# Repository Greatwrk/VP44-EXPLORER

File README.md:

# VP44 EXPLORER

My project replaces the control board that sits on top of the pump with a remote board.
The project uses an STM32f303 Nucleo dev. Board and I used Arduino IDE.
A custom PCB was made in two parts. One is the main logic and sensor interface. The second part is the 
solenoid drivers and power supply. The current driver board uses a high-speed switching buck converter
to operate the fuel solenoid. A linear drive board is under development.
The linear method is the OEM style. It generates a lot of heat and is cooled by the fuel flowing
under it in the pump housing. The switching method results in significantly less heat. The downside is the switching signal can
mask the current monitoring of the solenoid. As the armature plunger moves it causes a change in inductance which causes a small current blip.
The blip is useful to determine the solenoid dead time.

The VP44 shaft has a toothed wheel, the tooth spacing is 3 degrees of crankshaft rotation.
Every 60 degrees (120 at crankshaft) is a pair of staggered teeth.
These I refer to as the index tooth.
A dual magneto-resistive sensor with a back bias magnet senses the teeth as they pass by and creates two sinewaves.
The one that leads I refer to as phase A. The second follows by approximately 90 degrees, I refer to it as phase B.
Both signals are adaptive zero crossing detected by internal opAmps and the DACs in the STM32 and then fed to timer captures.
The software detects the index tooth region and resets a tooth edge counter to zero.
On the tooth edge 19 of the B phase the radial injection plungers are at their maximum extension.
As they follow the cam ring into compression it's at this position the injection solenoid valve must be fully transitioned to the closed position.
This is the start of injection SOI. After a variable amount of degrees, the valve de-energizes this is the end of injection EOI.

Since the solenoid has deadtime on both turn on and turn off the switching must occur before edge 19 or EOI actually happens.
This is done by computing shaft position, velocity, and acceleration to predict the relative time from a current tooth edge to edge 19.
Obviously, the closer we are to the edge 19 event the better the prediction will be, but at higher RPMs the deadtime of the solenoid results in the required prediction to
occur many degrees in advance else the valve will be closed too late or early.
That results in late injection, reduced fuel delivery and hazy smoke.
The valve must be de-energized before the moment of desired EOI because of mechanical delay I call this release time, which is about 850 microseconds.
The dead time is mostly dependent on the battery voltage and must be calculated often. 
A full current is applied to get the valve moving then the current is reduced to prevent the valve from slamming on its seat and bouncing.
Finally, the current is reduced to a safe level for the majority of the injection event.
The switch-off induction spike at EOI must be clamped at a higher voltage and low current for a fast release.
The magnetic field is determined largely by A x N turns, so keeping current low speeds the armature release.
Simple clamping / recirculating methods are too slow. A zener diode RC circuit is used. 
Some manual adjustments to times and current values must be determined with an oscilloscope and are stored.

Anyone who has kick-started or rope-started a small engine has experienced the rapid fluctuations that occur in 
crankshaft velocity. These also occur in a running engine but are greatly reduced by the flywheel mass
and inertia. These variations have to be accounted for in both the SOI time and EOI time if not the
engine will start to run rough which makes the variations worse and results in timing and delivery
errors and possible stalling or running away.

The timing advance is determined by the phase relationship of the cam ring to the crankshaft position.
The ECU decodes the crankshaft position sensor and cam sensor to create a reference signal that
occurs at 20 degrees after top dead center for each cylinder. Later engines removed the CKP and changed the camshaft gear. 
With my project, the decoding is done internally and the ECU is not required. 
The cam ring moves by a hydraulic piston which is controlled by another solenoid valve. It is PWM controlled by the MCU. 
The actual timing is calculated by the VP tooth signal phase relationship to the CKP-derived signal. 
A software servo control loop adjusts the PWM to match the computed timing with the desired timing contained in the usual look-up tables.

For now, the TPS, MAP and CKP are all that's required. The CMP is optional. A CAN interface is on the board and a CAN interface is being developed.
The Schematic and PCB were made with KiCad. The code has some low-level stuff for some of the peripherals that at the time were not supported by STM32duino.

If you build this I suggest using a 2 ohm 50 W resistor in place of the fuel solenoid for testing with a scope. The resistor can later be placed
in series with the solenoid to protect it on the bench while sweep testing at RPMs and Fuel levels. Listen for any malfunctions.
The power transistors must be isolated from the heatsink with silicon insulators. Always test isolation with an DVM.

# See it run [HERE](https://www.youtube.com/watch?v=DHwnkv7ZLJk)

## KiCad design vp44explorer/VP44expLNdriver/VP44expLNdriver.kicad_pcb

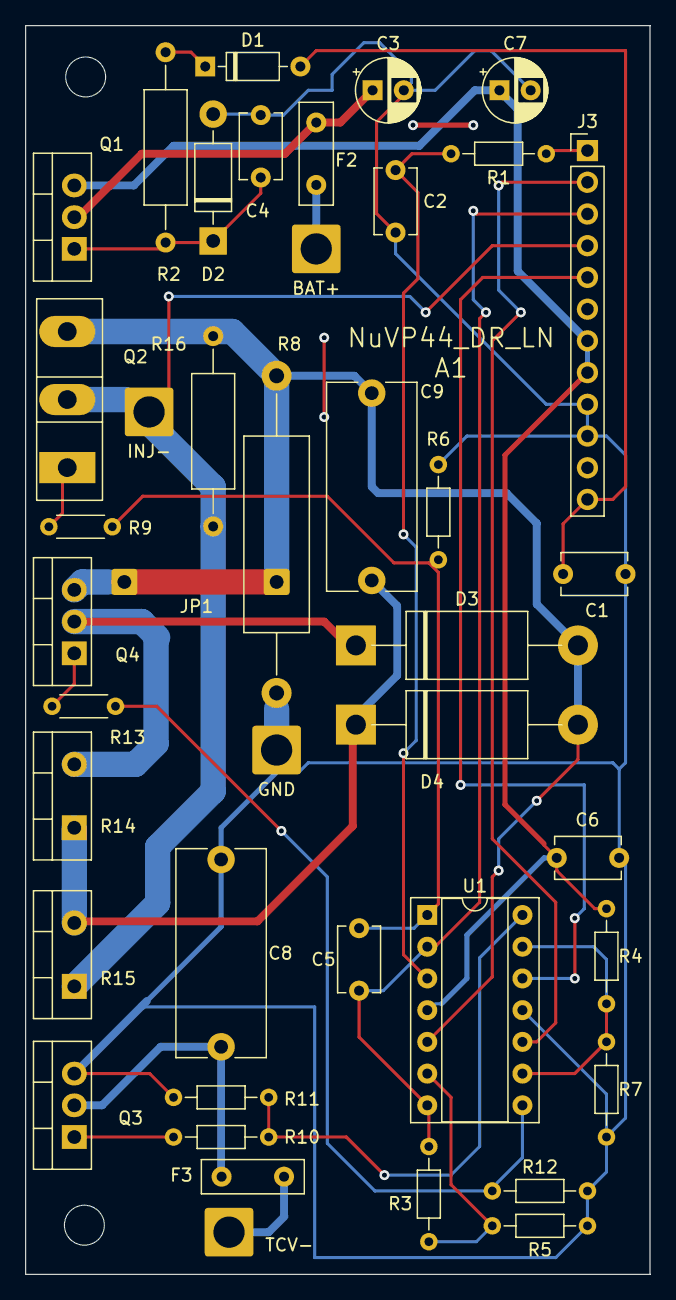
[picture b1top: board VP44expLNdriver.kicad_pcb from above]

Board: 2 copper layers, 50.0 x 100.0 mm, 45 parts (0 on the bottom side), 26 nets.

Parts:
C1, C4: 1uF; C_Disc_D5.1mm_W3.2mm_P5.00mm
C2, C6: 0.1uF; C_Disc_D5.1mm_W3.2mm_P5.00mm
C3, C7: 100uF; CP_Radial_D5.0mm_P2.50mm
C5: 100pF; C_Disc_D5.1mm_W3.2mm_P5.00mm
C8: 1uF; C_Rect_L16.5mm_W7.0mm_P15.00mm_MKT
C9: 0.1uF; C_Rect_L16.5mm_W7.0mm_P15.00mm_MKT
D1: 1N914B; D_DO-35_SOD27_P7.62mm_Horizontal
D2: 5.6V; D_DO-41_SOD81_P10.16mm_Horizontal
D3, D4: 31V; D_DO-201AD_P17.78mm_Horizontal
F2, F3: Polyfuse; C_Disc_D8.0mm_W2.5mm_P5.00mm
J1: GND; SolderWire-2sqmm_1x01_D2mm_OD3.9mm
J2: BAT+; SolderWire-2sqmm_1x01_D2mm_OD3.9mm
J3: Conn_01x12; PinHeader_1x12_P2.54mm_Vertical
J4: INJ-; SolderWire-2sqmm_1x01_D2mm_OD3.9mm
J5: TCV-; SolderWire-2sqmm_1x01_D2mm_OD3.9mm
J6, J7: TCV; SolderWire-0.5sqmm_1x01_D0.9mm_OD2.1mm
MH1, MH2: MountingHole_3.2mm_M3
Q1: MJF44H11G; TO-220-3_Vertical
Q2: IRF250P225; TO-247-3_Vertical
Q3: IRL2910; TO-220-3_Vertical
Q4: 75NF20; TO-220-3_Vertical
R1, R3, R4, R5, R6, R7, R11, R12: 10K; R_Axial_DIN0204_L3.6mm_D1.6mm_P7.62mm_Horizontal
R2, R16: 220R; R_Axial_DIN0309_L9.0mm_D3.2mm_P15.24mm_Horizontal
R8: .05R; R_Axial_DIN0516_L15.5mm_D5.0mm_P25.40mm_Horizontal
R9, R13: 100R; R_Axial_DIN0204_L3.6mm_D1.6mm_P5.08mm_Horizontal
R10: 100R; R_Axial_DIN0204_L3.6mm_D1.6mm_P7.62mm_Horizontal
R14, R15: 1R; TO-220-2_Vertical
U1: Opamp_Quad; DIP-14_W7.62mm_Socket

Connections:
+5V: C6.2, C7.1, J3.7, J3.8, Q1.3 (E), R4.1, U1.4 (V+)
+12V: C1.2, D1.2 (A), J3.12
GND: C1.1, C2.1, C3.2, C4.1, C6.1, C7.2, C8.1, D2.2 (A), J1.1, J3.9, J3.10, Q3.3 (S), R5.1, R6.2, R7.2, R8.2, R11.2, R12.2, U1.11 (V-)
unnamed: C5.2, R6.1, R9.1, U1.1
unnamed: D1.1 (K), R2.1
unnamed: C4.2, D2.1 (K), Q1.1 (B), R2.2
unnamed: C9.1, D3.2 (A), D4.2 (A), J6.1, J7.1, Q2.3 (S), Q4.3 (S), R8.1, R16.1, U1.5 (+)
unnamed: D3.1 (K), Q4.2 (D), R14.2
unnamed: C9.2, D4.1 (K), R14.1, R15.2
unnamed: F2.1, J2.1
unnamed: J3.1, R1.1
unnamed: J3.2, U1.10 (+)
unnamed: C5.1, J3.3, R3.1, U1.2 (-), U1.7
unnamed: J3.4, J4.1, Q2.2 (D), R15.1, R16.2
unnamed: J3.5, U1.12 (+)
unnamed: F3.2, J5.1
unnamed: C3.1, F2.2, Q1.2 (C)
unnamed: Q2.1 (G), R9.2
unnamed: C8.2, F3.1, Q3.2 (D)
unnamed: Q3.1 (G), R10.2
unnamed: Q4.1 (G), R13.1
unnamed: R10.1, R11.1, U1.14
unnamed: R12.1, R13.2, U1.8
unnamed: C2.2, R1.2, U1.3 (+)
unnamed: R3.2, R5.2, U1.6 (-)
unnamed: R4.2, R7.1, U1.9 (-), U1.13 (-)

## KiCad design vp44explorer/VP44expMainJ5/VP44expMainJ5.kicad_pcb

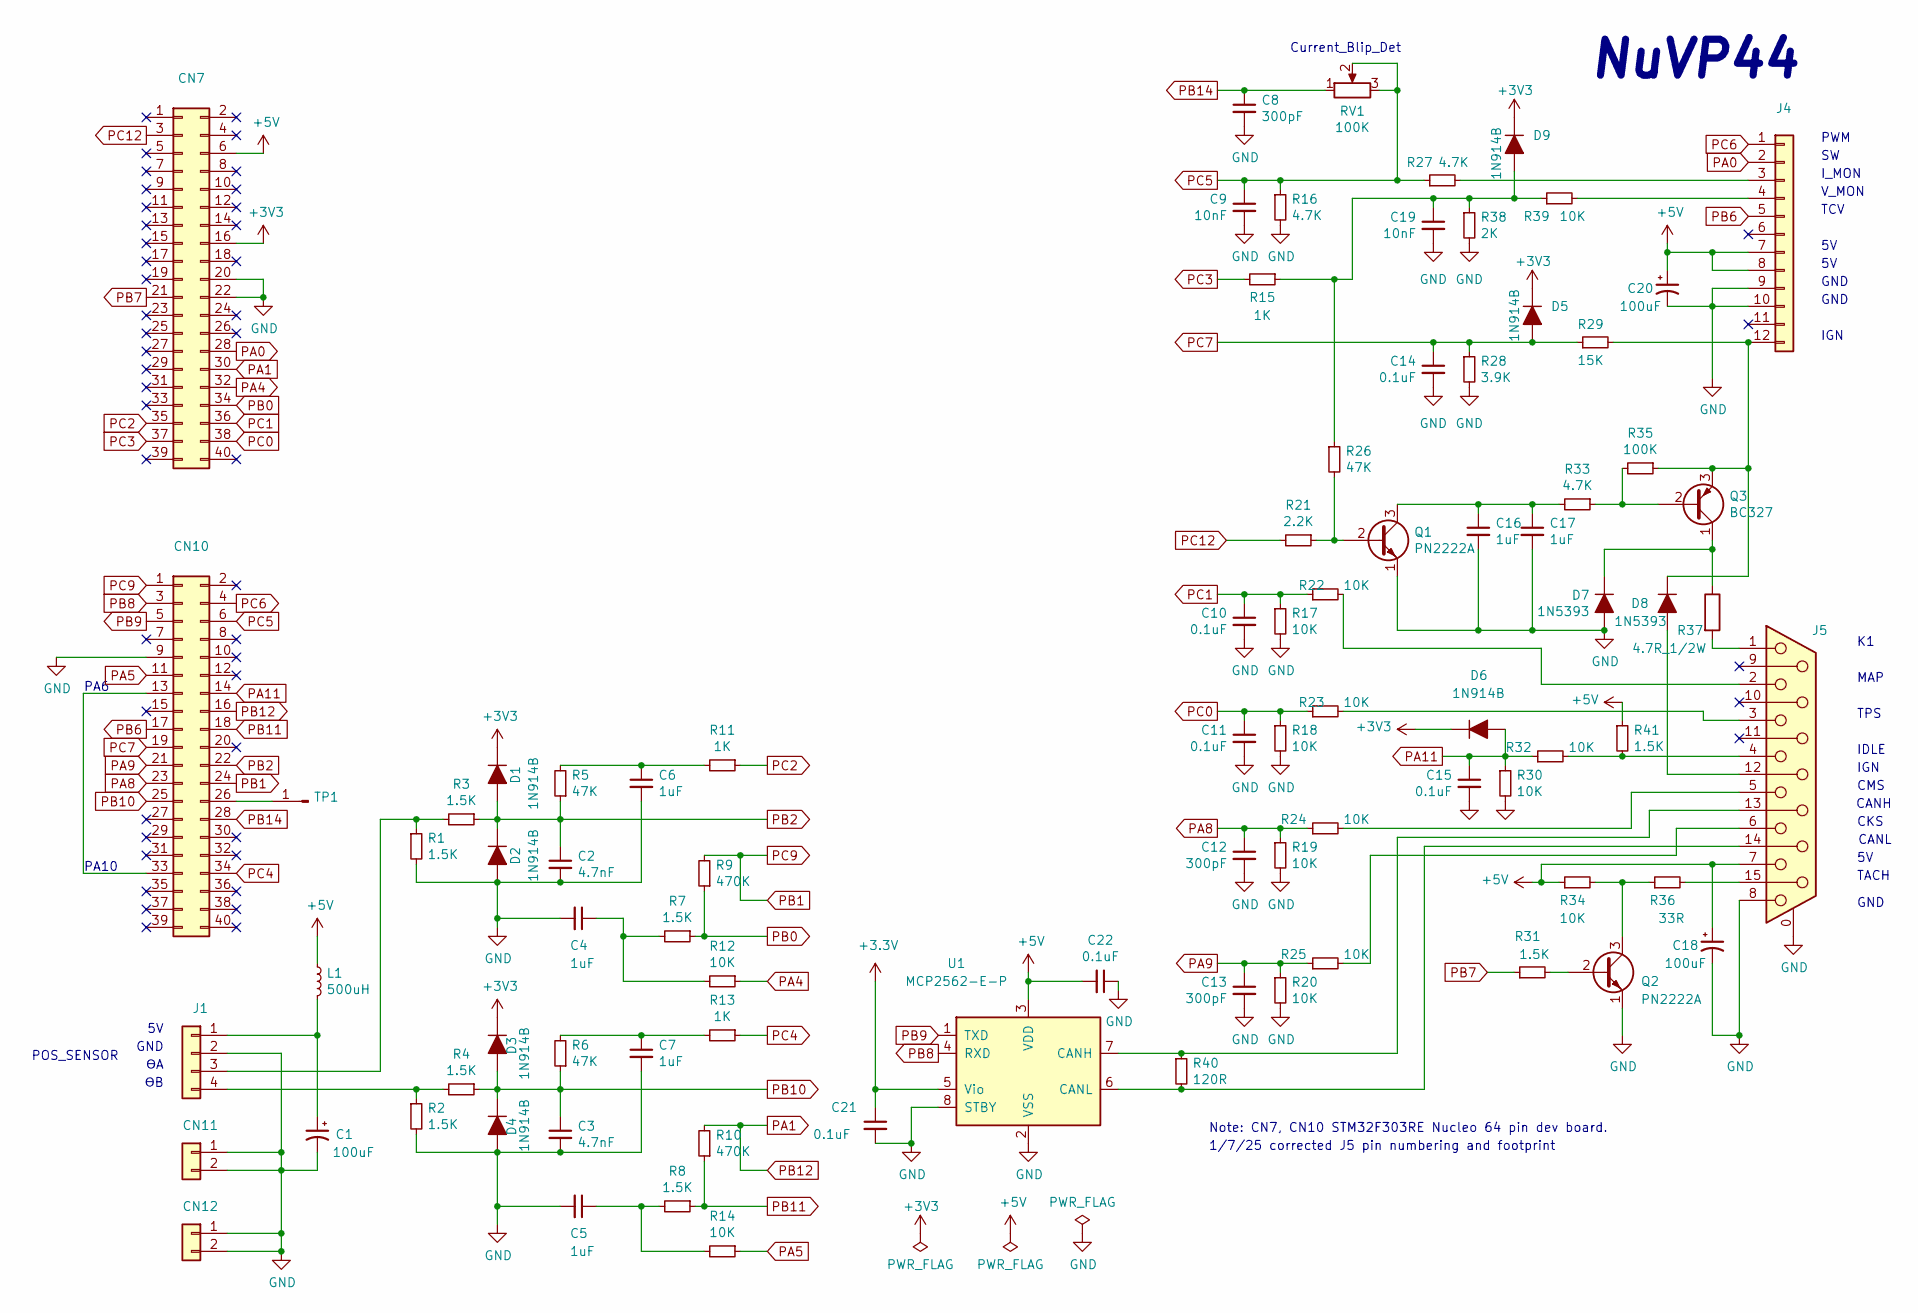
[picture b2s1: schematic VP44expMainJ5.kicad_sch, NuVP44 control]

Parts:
C1, C18, C20: 100uF; CP_Radial_D5.0mm_P2.50mm
C2, C3: 4.7nF; C_Disc_D5.0mm_W2.5mm_P5.00mm
C4, C5, C6, C7, C16, C17: 1uF; C_Disc_D5.1mm_W3.2mm_P5.00mm
C8, C12, C13: 300pF; C_Disc_D5.0mm_W2.5mm_P5.00mm
C9, C19: 10nF; C_Disc_D5.0mm_W2.5mm_P5.00mm
C10, C11, C14, C15, C21, C22: 0.1uF; C_Disc_D5.0mm_W2.5mm_P5.00mm
CN7, CN10: Conn_02x20_Odd_Even; PinHeader_2x20_P2.54mm_Vertical
CN11, CN12: Conn_01x02_Female; PinHeader_1x02_P2.54mm_Vertical
D1, D2, D3, D4, D5, D6, D9: 1N914B; D_DO-35_SOD27_P7.62mm_Horizontal
D7, D8: 1N5393; D_DO-41_SOD81_P12.70mm_Horizontal
J1: Conn_01x04_Shielded; PinHeader_1x04_P2.54mm_Vertical
J4: Conn_01x12; PinHeader_1x12_P2.54mm_Vertical
J5: DSUB-15_Female_Horizontal_P2.77x2.84mm_EdgePinOffset4.94mm_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
L1: 500uH; L_Axial_L11.0mm_D4.5mm_P5.08mm_Vertical_Fastron_MECC
Q1, Q2: PN2222A; TO-92_Inline
Q3: BC327; TO-92_Inline
R1, R2, R3, R4, R7, R8, R31, R41: 1.5K; R_Axial_DIN0204_L3.6mm_D1.6mm_P7.62mm_Horizontal
R5, R6, R26: 47K; R_Axial_DIN0204_L3.6mm_D1.6mm_P7.62mm_Horizontal
R9, R10: 470K; R_Axial_DIN0204_L3.6mm_D1.6mm_P7.62mm_Horizontal
R11, R13, R15: 1K; R_Axial_DIN0204_L3.6mm_D1.6mm_P7.62mm_Horizontal
R12, R14, R17, R18, R19, R20, R22, R23, R24, R25, R30, R32, R34, R39: 10K; R_Axial_DIN0204_L3.6mm_D1.6mm_P7.62mm_Horizontal
R16, R27, R33: 4.7K; R_Axial_DIN0204_L3.6mm_D1.6mm_P7.62mm_Horizontal
R21: 2.2K; R_Axial_DIN0204_L3.6mm_D1.6mm_P7.62mm_Horizontal
R28: 3.9K; R_Axial_DIN0204_L3.6mm_D1.6mm_P7.62mm_Horizontal
R29: 15K; R_Axial_DIN0204_L3.6mm_D1.6mm_P7.62mm_Horizontal
R35: 100K; R_Axial_DIN0204_L3.6mm_D1.6mm_P7.62mm_Horizontal
R36: 33R; R_Axial_DIN0204_L3.6mm_D1.6mm_P7.62mm_Horizontal
R37: 4.7R_1/2W; R_Axial_DIN0309_L9.0mm_D3.2mm_P15.24mm_Horizontal
R38: 2K; R_Axial_DIN0204_L3.6mm_D1.6mm_P7.62mm_Horizontal
R40: 120R; R_Axial_DIN0204_L3.6mm_D1.6mm_P7.62mm_Horizontal
RV1: 100K; Potentiometer_Bourns_3296W_Vertical
TP1: Conn_01x01_Male; PinHeader_1x01_P2.54mm_Vertical
U1: MCP2562-E-P; DIP-8_W7.62mm_Socket

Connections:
+5V: C18.1, C20.1, C22.2, CN7.6, J4.7, J4.8, J5.7, L1.1, R34.1, R41.1, U1.3 (VDD)
GND: C1.2, C2.2, C3.2, C4.2, C5.2, C6.2, C7.2, C8.2, C9.2, C10.2, C11.2, C12.2, C13.2, C14.2, C15.2, C16.2, C17.2, C18.2, C19.2, C20.2, C21.2, C22.1, CN7.20, CN7.22, CN10.9, CN11.1, CN11.2, CN12.1, CN12.2, D2.2 (A), D4.2 (A), D7.2 (A), J1.2, J4.9, J4.10, J5.0 (PAD), J5.8, Q1.1 (E), Q2.1 (E), R1.2, R2.2, R16.2, R17.2, R18.2, R19.2, R20.2, R28.2, R30.2, R38.2, U1.2 (VSS), U1.8 (STBY)
unnamed: C4.1, R7.2, R12.2
unnamed: C5.1, R8.2, R14.2
unnamed: C6.1, R5.2, R11.2
unnamed: C7.1, R6.2, R13.2
unnamed: CN10.13, CN10.33
unnamed: CN10.26, TP1.1
unnamed: D7.1 (K), Q3.1 (C), R37.1
unnamed: D8.2 (A), J5.12
unnamed: D8.1 (K), J4.12, Q3.3 (E), R29.2, R35.1
unnamed: C19.1, D9.2 (A), R15.1, R26.1, R38.1, R39.1
unnamed: C1.1, J1.1, L1.2
unnamed: J1.3, R1.1, R3.2
unnamed: J1.4, R2.1, R4.2
unnamed: J4.3, R27.2
unnamed: J4.4, R39.2
unnamed: J5.13, R40.1, U1.7 (CANH)
unnamed: J5.14, R40.2, U1.6 (CANL)
unnamed: J5.15, R36.2
unnamed: J5.1, R37.2
unnamed: J5.2, R22.2
unnamed: J5.3, R23.2
unnamed: J5.4, R32.2, R41.2
unnamed: J5.5, R24.2
unnamed: J5.6, R25.2
unnamed: Q1.2 (B), R21.1, R26.2
unnamed: C16.1, C17.1, Q1.3 (C), R33.2
unnamed: Q2.2 (B), R31.2
unnamed: Q2.3 (C), R34.2, R36.1
unnamed: Q3.2 (B), R33.1, R35.2
PA0: CN7.28, J4.2
PA1: CN7.30, CN10.16, R10.2
PA4: CN7.32, R12.1
PA5: CN10.11, R14.1
PA8: C12.1, CN10.23, R19.1, R24.1
PA9: C13.1, CN10.21, R20.1, R25.1
PA11: C15.1, CN10.14, D6.2 (A), R30.1, R32.1
PB0: CN7.34, R7.1, R9.1
PB1: CN10.1, CN10.24, R9.2
PB2: C2.1, CN10.22, D1.2 (A), D2.1 (K), R3.1, R5.1
PB6: CN10.17, J4.5
PB7: CN7.21, R31.1
PB8: CN10.3, U1.4 (RXD)
PB9: CN10.5, U1.1 (TXD)
PB10: C3.1, CN10.25, D3.2 (A), D4.1 (K), R4.1, R6.1
PB11: CN10.18, R8.1, R10.1
PB14: C8.1, CN10.28, RV1.1
PC0: C11.1, CN7.38, R18.1, R23.1
PC1: C10.1, CN7.36, R17.1, R22.1
PC2: CN7.35, R11.1
PC3: CN7.37, R15.2
PC4: CN10.34, R13.1
PC5: C9.1, CN10.6, R16.1, R27.1, RV1.2, RV1.3
PC6: CN10.4, J4.1
PC7: C14.1, CN10.19, D5.2 (A), R28.1, R29.1
PC12: CN7.3, R21.2

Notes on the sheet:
Note: CN7, CN10 STM32F303RE Nucleo 64 pin dev board.
IGN
GND
I_MON
CANL
PA10
NuVP44
Current_Blip_Det
PA6
CMS
TCV
TACH
1/7/25 corrected J5 pin numbering and footprint
V_MON
IDLE
PWM
POS_SENSOR
CKS
TPS
MAP
CANH

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
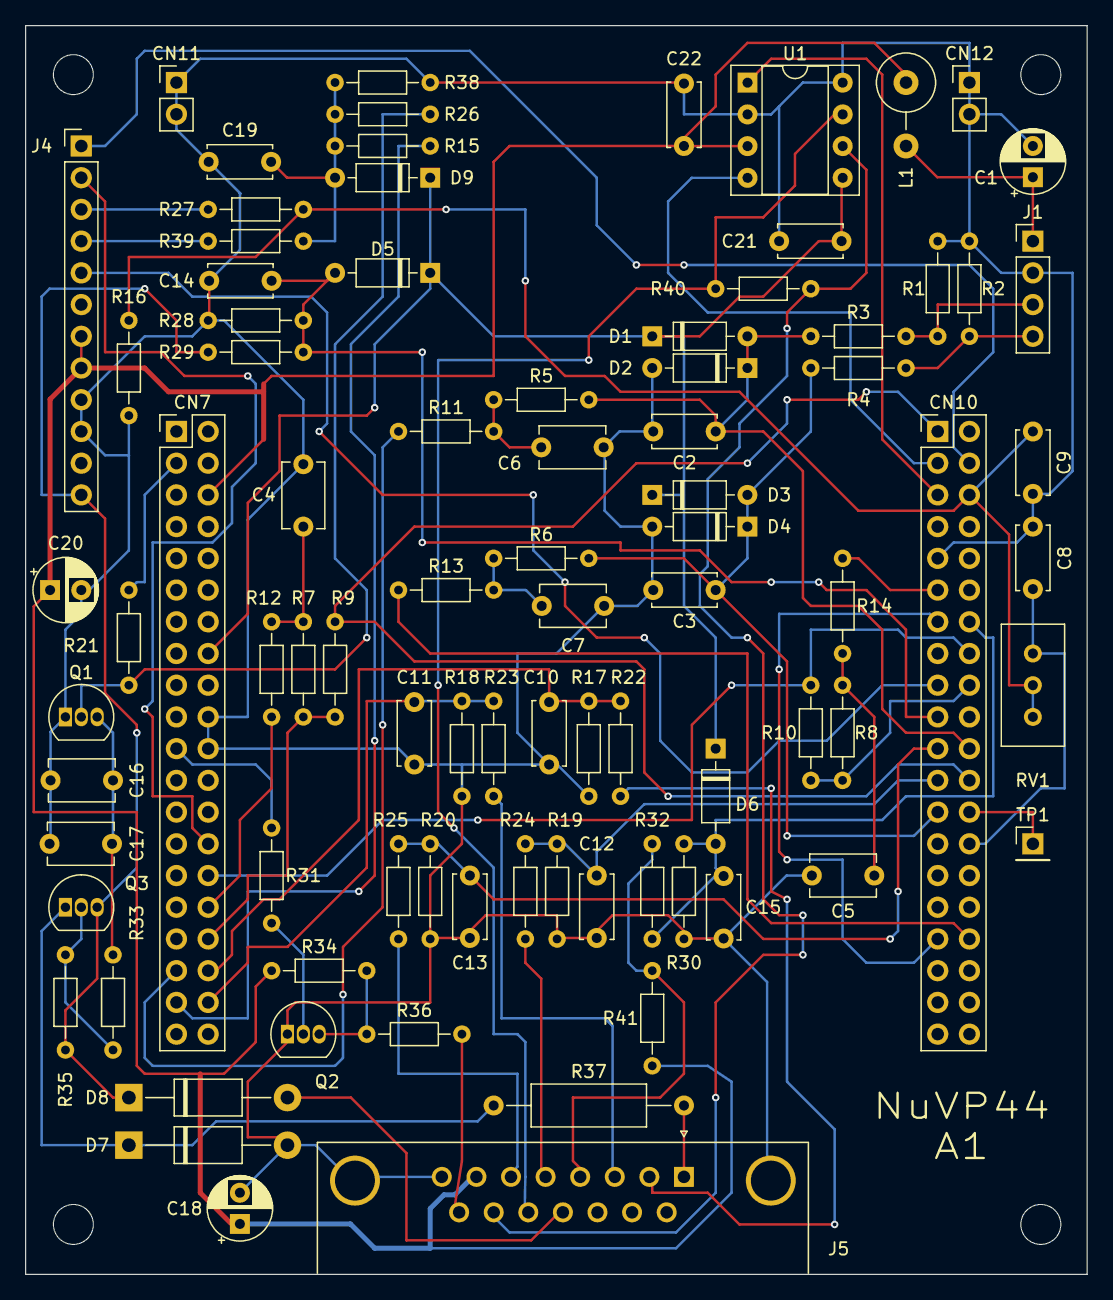
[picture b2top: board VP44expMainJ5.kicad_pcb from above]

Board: 2 copper layers, 85.0 x 100.0 mm, 90 parts (0 on the bottom side), 58 nets.

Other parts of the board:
MH1, MH2, MH3, MH4: MountingHole_3.2mm_M3

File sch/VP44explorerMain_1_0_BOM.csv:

"Reference","Value","Footprint","Datasheet","Qty"
"C1, C18, C20","100uF","Capacitor_THT:CP_Radial_D5.0mm_P2.50mm","~","3"
"C2, C3","4.7nF","Capacitor_THT:C_Disc_D5.0mm_W2.5mm_P5.00mm","~","2"
"C4-C7, C16, C17","1uF","Capacitor_THT:C_Disc_D5.1mm_W3.2mm_P5.00mm","~","6"
"C8, C12, C13","300pF","Capacitor_THT:C_Disc_D5.0mm_W2.5mm_P5.00mm","~","3"
"C9, C19","10nF","Capacitor_THT:C_Disc_D5.0mm_W2.5mm_P5.00mm","~","2"
"C10, C11, C14, C15, C21, C22","0.1uF","Capacitor_THT:C_Disc_D5.0mm_W2.5mm_P5.00mm","~","6"
"CN7, CN10","Conn_02x20_Odd_Even","Connector_PinHeader_2.54mm:PinHeader_2x20_P2.54mm_Vertical","~","2"
"CN11, CN12","Conn_01x02_Female","Connector_PinHeader_2.54mm:PinHeader_1x02_P2.54mm_Vertical","~","2"
"D1-D6, D9","1N914B","Diode_THT:D_DO-35_SOD27_P7.62mm_Horizontal","~","7"
"D7, D8","1N5393","Diode_THT:D_DO-41_SOD81_P12.70mm_Horizontal","~","2"
"J1","Conn_01x04_Shielded","Connector_PinHeader_2.54mm:PinHeader_1x04_P2.54mm_Vertical","~","1"
"J4","Conn_01x12","Connector_PinHeader_2.54mm:PinHeader_1x12_P2.54mm_Vertical","~","1"
"J5","DB15_Male_MountingHoles","Connector_Dsub:DSUB-15_Male_Horizontal_P2.77x2.84mm_EdgePinOffset4.94mm_Housed_MountingHolesOffset7.48mm","digikey 182-15FE-ND , MFR 182-015-213R531","1"
"L1","500uH","Inductor_THT:L_Axial_L11.0mm_D4.5mm_P5.08mm_Vertical_Fastron_MECC","~","1"
"Q1, Q2","PN2222A","Package_TO_SOT_THT:TO-92_Inline","http://www.fairchildsemi.com/ds/PN/PN2222A.pdf","2"
"Q3","BC327","Package_TO_SOT_THT:TO-92_Inline","http://www.onsemi.com/pub_link/Collateral/BC327-D.PDF","1"
"R1-R4, R7, R8, R31, R41","1.5K","Resistor_THT:R_Axial_DIN0204_L3.6mm_D1.6mm_P7.62mm_Horizontal","~","8"
"R5, R6, R26","47K","Resistor_THT:R_Axial_DIN0204_L3.6mm_D1.6mm_P7.62mm_Horizontal","~","3"
"R9, R10","470K","Resistor_THT:R_Axial_DIN0204_L3.6mm_D1.6mm_P7.62mm_Horizontal","~","2"
"R11, R13, R15","1K","Resistor_THT:R_Axial_DIN0204_L3.6mm_D1.6mm_P7.62mm_Horizontal","~","3"
"R12, R14, R17-R20, R22-R25, R30, R32, R34, R39","10K","Resistor_THT:R_Axial_DIN0204_L3.6mm_D1.6mm_P7.62mm_Horizontal","~","14"
"R16, R27, R33","4.7K","Resistor_THT:R_Axial_DIN0204_L3.6mm_D1.6mm_P7.62mm_Horizontal","~","3"
"R21","2.2K","Resistor_THT:R_Axial_DIN0204_L3.6mm_D1.6mm_P7.62mm_Horizontal","~","1"
"R28","3.9K","Resistor_THT:R_Axial_DIN0204_L3.6mm_D1.6mm_P7.62mm_Horizontal","~","1"
"R29","15K","Resistor_THT:R_Axial_DIN0204_L3.6mm_D1.6mm_P7.62mm_Horizontal","~","1"
"R35","100K","Resistor_THT:R_Axial_DIN0204_L3.6mm_D1.6mm_P7.62mm_Horizontal","~","1"
"R36","33R","Resistor_THT:R_Axial_DIN0204_L3.6mm_D1.6mm_P7.62mm_Horizontal","~","1"
"R37","4.7R_1/2W","Resistor_THT:R_Axial_DIN0309_L9.0mm_D3.2mm_P15.24mm_Horizontal","~","1"
"R38","2K","Resistor_THT:R_Axial_DIN0204_L3.6mm_D1.6mm_P7.62mm_Horizontal","~","1"
"R40","120R","Resistor_THT:R_Axial_DIN0204_L3.6mm_D1.6mm_P7.62mm_Horizontal","~","1"
"RV1","100K","Potentiometer_THT:Potentiometer_Bourns_3296W_Vertical","~","1"
"TP1","Conn_01x01_Male","Connector_PinHeader_2.54mm:PinHeader_1x01_P2.54mm_Vertical","~","1"
"U1","MCP2562-E-P","Package_DIP:DIP-8_W7.62mm_Socket","http://ww1.microchip.com/downloads/en/DeviceDoc/25167A.pdf","1"

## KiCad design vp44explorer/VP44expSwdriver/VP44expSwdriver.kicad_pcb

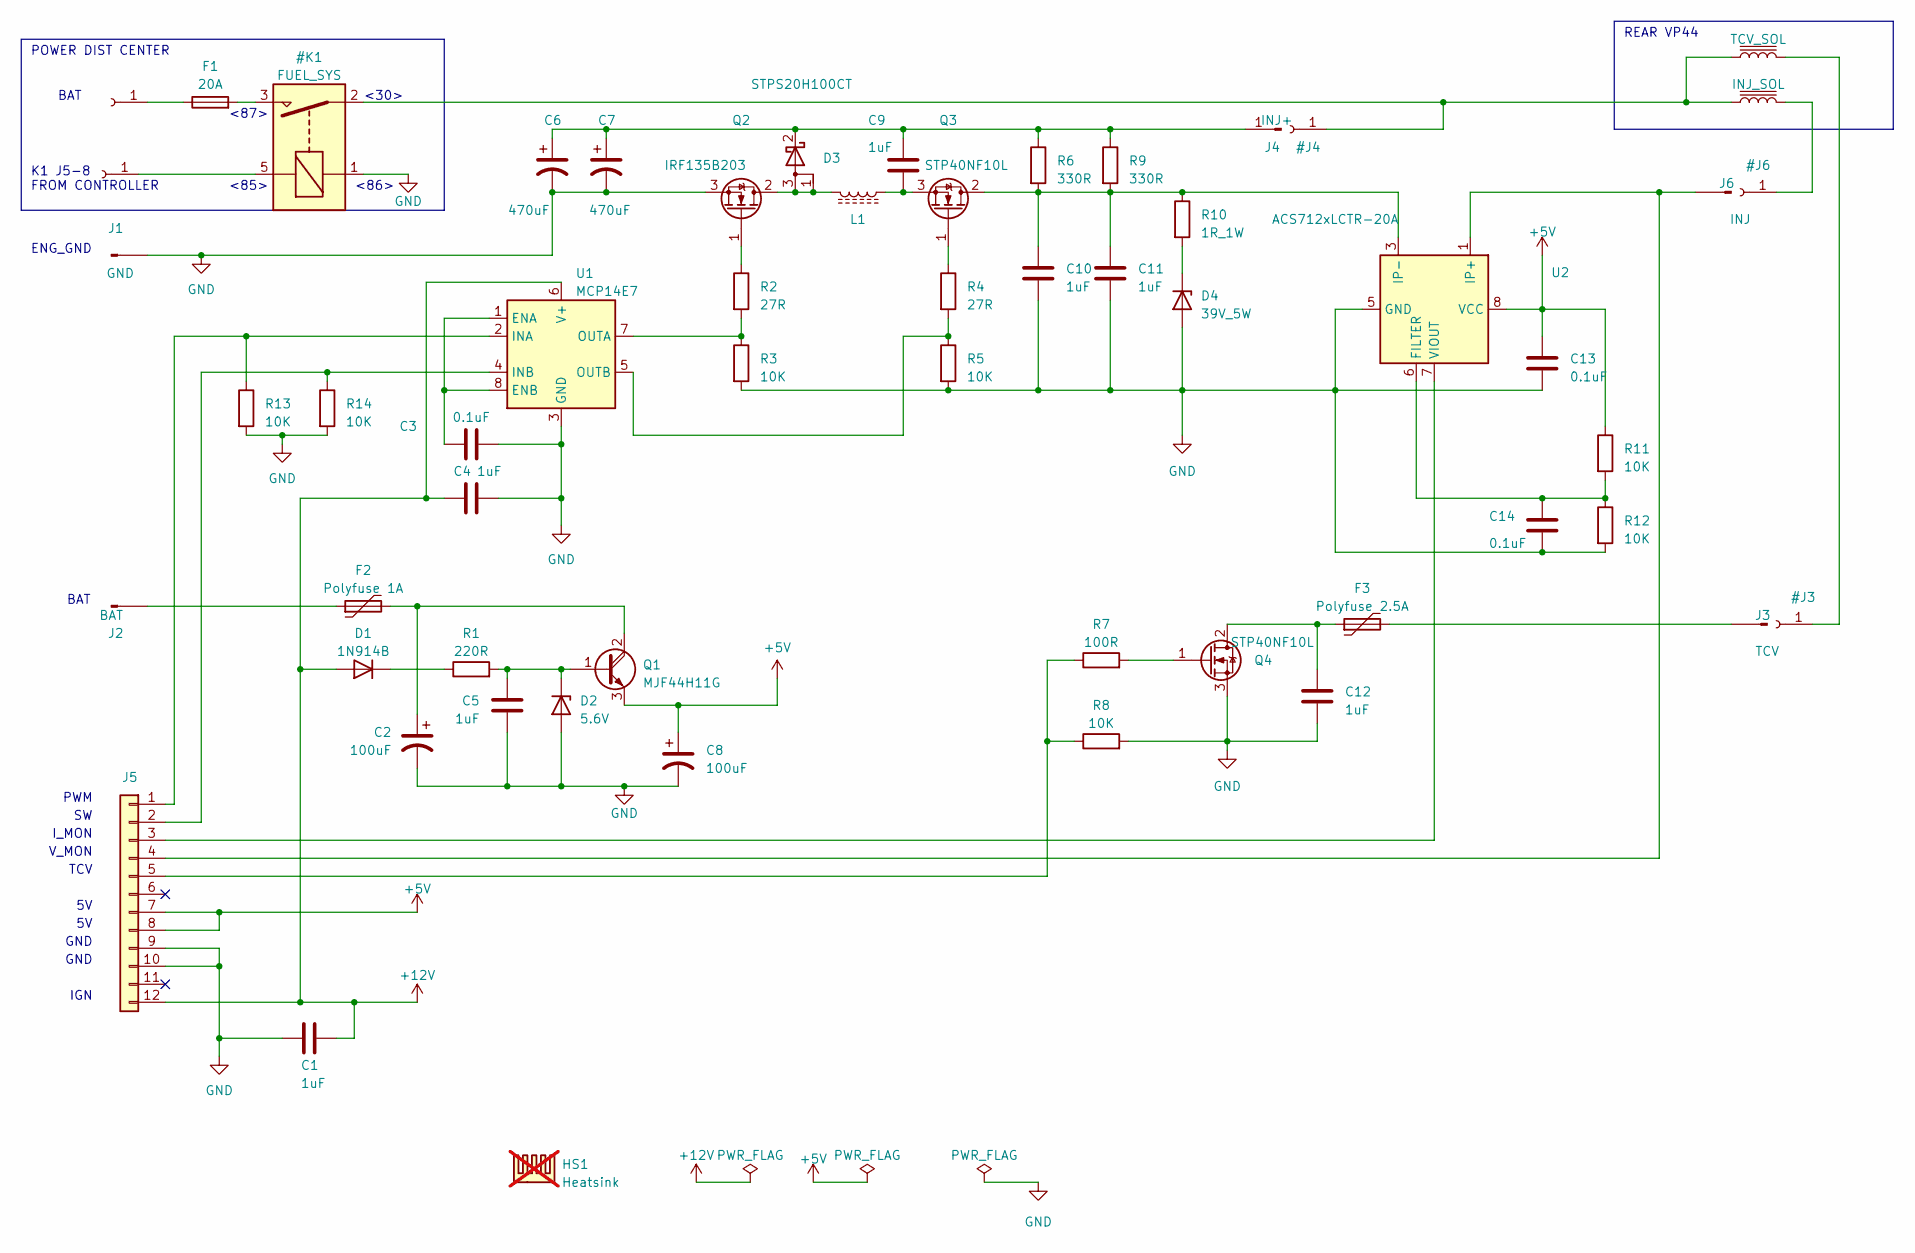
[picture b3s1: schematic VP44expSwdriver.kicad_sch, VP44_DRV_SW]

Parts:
C1, C4, C5: 1uF; C_Disc_D5.1mm_W3.2mm_P5.00mm
C2, C8: 100uF; CP_Radial_D5.0mm_P2.50mm
C3, C13, C14: 0.1uF; C_Disc_D5.0mm_W2.5mm_P5.00mm
C6, C7: 470uF; CP_Radial_D8.0mm_P5.00mm
C9, C10, C11, C12: 1uF; C_Rect_L16.5mm_W7.0mm_P15.00mm_MKT
D1: 1N914B; D_DO-35_SOD27_P7.62mm_Horizontal
D2: 5.6V; D_DO-41_SOD81_P10.16mm_Horizontal
D3: STPS20H100CT; TO-220-3_Vertical
D4: 39V_5W; D_DO-201AD_P15.24mm_Horizontal
F1: 20A; Automotive ATC
F2: Polyfuse 1A; C_Disc_D8.0mm_W2.5mm_P5.00mm
F3: Polyfuse 2.5A; C_Disc_D8.0mm_W2.5mm_P5.00mm
HS1: Heatsink; 100 X 40 X20 AMAZON.COM; not fitted
J1: GND; SolderWire-2sqmm_1x01_D2mm_OD3.9mm
J2: BAT; SolderWire-2sqmm_1x01_D2mm_OD3.9mm
J3: TCV; SolderWire-2sqmm_1x01_D2mm_OD3.9mm
J4: INJ+; SolderWire-2sqmm_1x01_D2mm_OD3.9mm
J5: Conn_01x12; PinHeader_1x12_P2.54mm_Vertical
J6: INJ; SolderWire-2sqmm_1x01_D2mm_OD3.9mm
L1: L_Ferrite; L_Toroid_Vertical_L26.7mm_W14.0mm_P10.16mm_Pulse_D
L2: TCV_SOL
L3: INJ_SOL
Q1: MJF44H11G; TO-220-3_Vertical
Q2: IRF135B203; TO-220-3_Vertical
Q3, Q4: STP40NF10L; TO-220-3_Vertical
R1: 220R; R_Axial_DIN0309_L9.0mm_D3.2mm_P15.24mm_Horizontal
R2, R4: 27R; R_Axial_DIN0204_L3.6mm_D1.6mm_P7.62mm_Horizontal
R3, R5, R8, R11, R12, R13, R14: 10K; R_Axial_DIN0204_L3.6mm_D1.6mm_P7.62mm_Horizontal
R6, R9: 330R; R_Axial_DIN0309_L9.0mm_D3.2mm_P15.24mm_Horizontal
R7: 100R; R_Axial_DIN0204_L3.6mm_D1.6mm_P7.62mm_Horizontal
R10: 1R_1W; R_Axial_DIN0414_L11.9mm_D4.5mm_P20.32mm_Horizontal
U1: MCP14E7; DIP-8_W7.62mm
U2: ACS712xLCTR-20A; SOIC-8_3.9x4.9mm_P1.27mm

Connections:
+5V: C8.1, C13.1, J5.7, J5.8, Q1.3 (E), R11.1, U2.8 (VCC)
+12V: C1.2, C4.1, D1.2 (A), J5.12, U1.6 (V+)
GND: C1.1, C2.2, C3.1, C4.2, C5.1, C6.2, C7.2, C8.2, C10.2, C11.2, C12.1, C13.2, C14.2, D2.2 (A), D4.2 (A), F1.1, F1.2, J1.1, J5.9, J5.10, L2.1, L2.2, L3.1, L3.2, Q2.3 (S), Q4.3 (S), R3.2, R5.2, R8.2, R12.2, R13.2, R14.2, U1.3 (GND), U2.5 (GND)
unnamed: D1.1 (K), R1.1
unnamed: C5.2, D2.1 (K), Q1.1 (B), R1.2
unnamed: C6.1, C7.1, C9.2, D3.2 (K), J4.1, R6.1, R9.1
unnamed: D4.1 (K), R10.2
unnamed: F2.1, J2.1
unnamed: F3.2, J3.1
unnamed: J5.1, R13.1, U1.2 (INA)
unnamed: J5.2, R14.1, U1.4 (INB)
unnamed: J5.3, U2.7 (VIOUT)
unnamed: J5.4, J6.1, U2.1 (IP+), U2.2 (IP+)
unnamed: J5.5, R7.1, R8.1
unnamed: C2.1, F2.2, Q1.2 (C)
unnamed: D3.1 (A), D3.3 (A), L1.2, Q2.2 (D)
unnamed: Q2.1 (G), R2.1
unnamed: C10.1, C11.1, Q3.2 (D), R6.2, R9.2, R10.1, U2.3 (IP-), U2.4 (IP-)
unnamed: Q3.1 (G), R4.1
unnamed: C9.1, L1.1, Q3.3 (S)
unnamed: C12.2, F3.1, Q4.2 (D)
unnamed: Q4.1 (G), R7.2
unnamed: C3.2, U1.1 (ENA), U1.8 (ENB)
unnamed: R2.2, R3.1, U1.7 (OUTA)
unnamed: R4.2, R5.1, U1.5 (OUTB)
unnamed: C14.1, R11.2, R12.1, U2.6 (FILTER)

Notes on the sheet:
POWER DIST CENTER
I_MON
TCV
IGN
V_MON
ENG_GND
K1 J5-8 FROM CONTROLLER
<86>
<85>
BAT
GND
REAR VP44
<87>
<30>
PWM

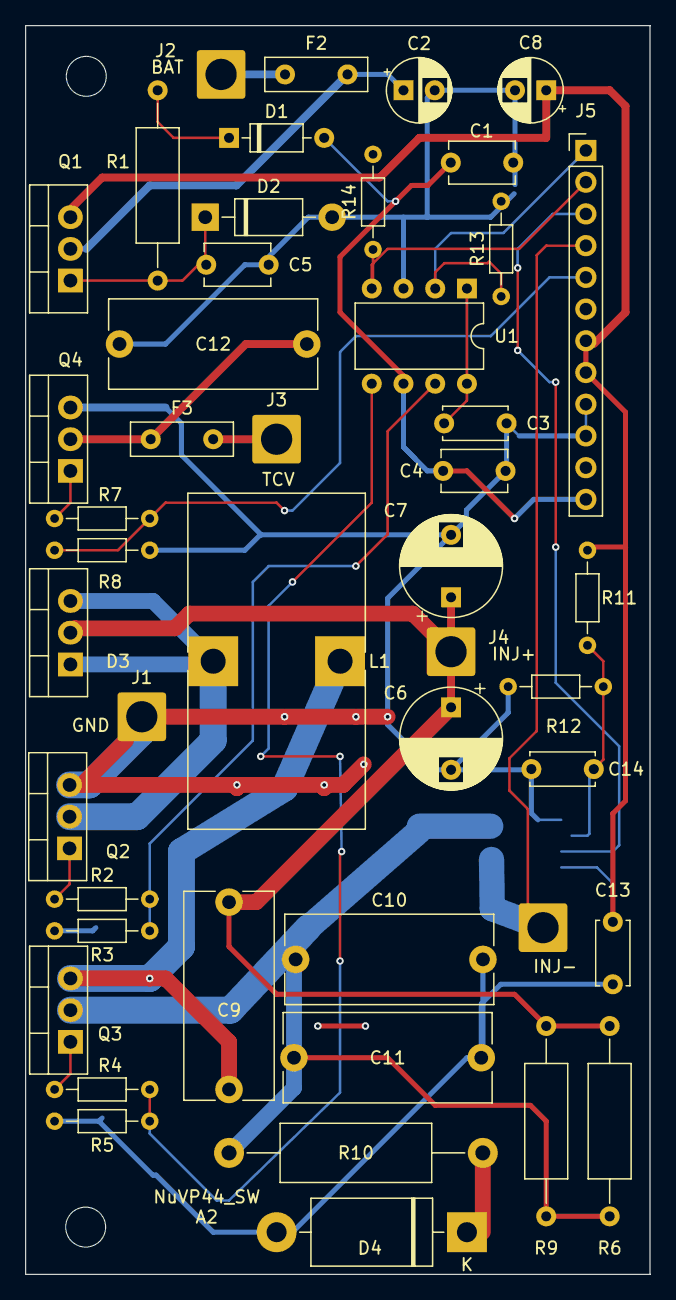
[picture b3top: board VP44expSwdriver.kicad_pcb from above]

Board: 2 copper layers, 50.0 x 100.0 mm, 49 parts (1 on the bottom side), 26 nets.

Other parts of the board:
MH1, MH2: MountingHole_3.2mm_M3

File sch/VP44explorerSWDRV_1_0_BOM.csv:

"Reference","Value","Footprint","Datasheet","Field4","Sim.Device","Sim.Pins","Sim.Type","Qty"
"C1, C4, C5","1uF","Capacitor_THT:C_Disc_D5.1mm_W3.2mm_P5.00mm","~","","","","","3"
"C2, C8","100uF","Capacitor_THT:CP_Radial_D5.0mm_P2.50mm","~","","","","","2"
"C3, C13, C14","0.1uF","Capacitor_THT:C_Disc_D5.0mm_W2.5mm_P5.00mm","~","","","","","3"
"C6, C7","470uF","Capacitor_THT:CP_Radial_D8.0mm_P5.00mm","~","","","","","2"
"C9-C12","1uF","Capacitor_THT:C_Rect_L16.5mm_W7.0mm_P15.00mm_MKT","DigiKey EF2105-ND, MFR# ECQ-E2105KF hi quality film cap only","","","","","4"
"D1","1N914B","Diode_THT:D_DO-35_SOD27_P7.62mm_Horizontal","~","","D","1=K 2=A","","1"
"D2","5.6V","Diode_THT:D_DO-41_SOD81_P10.16mm_Horizontal","~","","","","","1"
"D3","D_Schottky_AKA","Package_TO_SOT_THT:TO-220-3_Vertical","~","","","","","1"
"D4","39V_5W","Diode_THT:D_DO-201AD_P15.24mm_Horizontal","~","","","","","1"
"F1","20A","","~","","","","","1"
"F2, F3","Polyfuse","Capacitor_THT:C_Disc_D8.0mm_W2.5mm_P5.00mm","~","","","","","2"
"J1","GND","Connector_Wire:SolderWire-2sqmm_1x01_D2mm_OD3.9mm","~","","","","","1"
"J2","BAT","Connector_Wire:SolderWire-2sqmm_1x01_D2mm_OD3.9mm","~","","","","","1"
"J3","TCV","Connector_Wire:SolderWire-2sqmm_1x01_D2mm_OD3.9mm","~","","","","","1"
"J4","INJ+","Connector_Wire:SolderWire-2sqmm_1x01_D2mm_OD3.9mm","~","","","","","1"
"J5","Conn_01x12","Connector_PinHeader_2.54mm:PinHeader_1x12_P2.54mm_Vertical","~","","","","","1"
"J6","INJ","Connector_Wire:SolderWire-2sqmm_1x01_D2mm_OD3.9mm","~","INJ-","","","","1"
"L1","L_Ferrite","Inductor_THT:L_Toroid_Vertical_L26.7mm_W14.0mm_P10.16mm_Pulse_D","Amazon.com DC 300W 20A step down buck converter, re used coil","","","","","1"
"L2","TCV_SOL","","~","","","","","1"
"L3","INJ_SOL","","~","","","","","1"
"Q1","MJF44H11G","Package_TO_SOT_THT:TO-220-3_Vertical","https://www.onsemi.com/pub/Collateral/BDW93C-D.pdf","","","","","1"
"Q2","75NF20","Package_TO_SOT_THT:TO-220-3_Vertical","https://www.st.com/resource/en/datasheet/stp40n60m2.pdf","","NMOS","1=D 2=G 3=S","VDMOS","1"
"Q3","STP40NF10L","Package_TO_SOT_THT:TO-220-3_Vertical","https://www.st.com/resource/en/datasheet/stp40n60m2.pdf","","NMOS","1=D 2=G 3=S","VDMOS","1"
"Q4","IRL2910","Package_TO_SOT_THT:TO-220-3_Vertical","https://www.st.com/resource/en/datasheet/stp40n60m2.pdf","","NMOS","1=D 2=G 3=S","VDMOS","1"
"R1","220R","Resistor_THT:R_Axial_DIN0309_L9.0mm_D3.2mm_P15.24mm_Horizontal","~","","","","","1"
"R2, R4","27R","Resistor_THT:R_Axial_DIN0204_L3.6mm_D1.6mm_P7.62mm_Horizontal","~","","","","","2"
"R3, R5, R8, R11-R14","10K","Resistor_THT:R_Axial_DIN0204_L3.6mm_D1.6mm_P7.62mm_Horizontal","~","","","","","7"
"R6, R9","330R","Resistor_THT:R_Axial_DIN0309_L9.0mm_D3.2mm_P15.24mm_Horizontal","~","","","","","2"
"R7","100R","Resistor_THT:R_Axial_DIN0204_L3.6mm_D1.6mm_P7.62mm_Horizontal","~","","","","","1"
"R10","1R_1W","Resistor_THT:R_Axial_DIN0414_L11.9mm_D4.5mm_P20.32mm_Horizontal","~","","","","","1"
"U1","MCP14E7","Package_DIP:DIP-8_W7.62mm","http://ww1.microchip.com/downloads/en/DeviceDoc/MCP14E7.pdf","","","","","1"
"U2","ACS712xLCTR-20A","Package_SO:SOIC-8_3.9x4.9mm_P1.27mm","http://www.allegromicro.com/~/media/Files/Datasheets/ACS712-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","","","","","1"

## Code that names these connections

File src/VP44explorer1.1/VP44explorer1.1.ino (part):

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  expanded timer 2 and edge counters for future 4 cylinder.

   Pin assignments
   PA0 inj drive out timer2
   PA1 phase B trigger in
   PA2 USART2 TX to ST-link serial to USB converter
   PA3 USART2 RX ^
   PA6 OPAMP2 out inj. sol. monitor blip
   PA8 Cam position sensor, early 24 valve engines
   PA9 Crankshaft position sensor into timer2 ,early 24 valve engines
   PA10 solenoid current capture into timer2 ch 4 from OPAMP2 out
   PA11 idle validation in IDLE = 5V, pedal pressed = 0V
   PB0 OPAMP3 + in adaptive threshold from PC6
   PB1 OPAMP3 out wired to PC9 Testpoint 2
   PB2 OPAMP3 - in phase A from speed sensor
   PB6 timing control valve drive out (PWM)
   PB7 Tachometer square wave out RPM * 2 to PCM
   PB10 OPAMP4 - in: phase B from speed sensor
   PB11 OPAMP4 + in: adaptive threshold from PC8
   PB12 OPAMP4 out wired to PA1 Testpoint1
   PB13 inj solenoid drive current to ADC3 ch5 in
   PB14 Injection solenoid monitor OPAMP2 +in
   PB15 O'scope debug out
   PC0 TPS
   PC1 MAP
   PC2 Phase A ADC in
   PC3 Injection solenoid -
   PC4 Phase B ADC in
   PC5 OPAMP2 - in blip detector and ADC2 ch 11 current in
   PC6 PWM sol drive
   PC7 Ignition on sens
   PC8 spare
   PC9 Phase A trigger in
   PC10 USART3 TX to CCD bus future use
   PC11 USART3 RX to CCD bus future use
   PC12 Fuel system relay drive
*/

#define ON 0X3110;                         //Timer 2 compare Ch. 1 register pin states on match high
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#define scopeLow GPIOB->BRR = 0X8000;      // PB15 off - fast method O-scope goes low
#define scopeHigh GPIOB->BSRR = 0X8000;    //PB15 sync to O-scope goes high
#define scopeToggle GPIOB->ODR ^= 0X8000;  //PB15 sync to O-scope toggle
#define TACHhigh GPIOB->BSRR = 0X0080;     //Tach signal output PB7 high inverted at connector;
#define TACHlow GPIOB->BRR = 0X0080;       // PB7 Tach signal low - inverted at conn;

volatile uint32_t phaseA[60];
volatile uint32_t phaseB[60], phaseBpredict[60];
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const int FiringOrd[]{ 0, 1, 5, 3, 6, 2, 4 };   //4 cyl 0, 1, 3, 4, 2

const uint8_t
  phaseB_in = PA1,
  CMP = PA8,
  idle = PA11,
  phaseA_in = PB3,
  TACH = PB7,
  O_scope = PB15,
  IGN = PC7,
  failsafe = PC12,
  button = PC13;

void setup() {
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  //could possibly be done with low level - NVIC controller
  // Timer 2 is 32 bits wide but has no default pins so pins have to be remapped as ALT FUNC.
  // Timer 2 see datasheet table 14
  GPIOA->AFR[0] |= 0x00000011;  //AF1; PA0 Timer 2 ch 1, PA1 ch 2
  GPIOA->AFR[1] |= 0x00000AA0;  //AF10; PA9 Timer 2 ch 3, PA10 ch 4
  GPIOA->MODER |= 0x00280F0A;   //PA0, PA1 and PA9, PA10 pins set mode alt function.

  TIM2->CR1 = 0X0004;  //INTERNAL CLK, UPCOUNTER, UEV INTERRUPT ENABLED
  TIM2->PSC = 35;      //0.5 micro sec per tick
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  TIM2->CCMR1 = 0x3130;  //T2C1 force comp out low. T2C2 input capture. WAS 40
  TIM2->CCMR2 = 0X3131;  //input capture ch 3 N8 filter , ch 4 capture
  //the two previous steps have to be done before enabling the channels in the next register below
  TIM2->CCER = 0X3BB1;  // ch1 output compare to pin PA0, ch2 either edge, ch4 capture - edge, ch3 capture any edge was13B1
  TIM2->CCR1 = 600001;  //COMPARE TIMER TO 600001 micro seconds un-reachable

  //****** timer2 interrupts enable *********
  MainTim2->attachInterrupt(T2_OVF);        //Tim2 timeout 300 mS. about 90 RPM
  MainTim2->attachInterrupt(1, T2C1_comp);  //Solenoid driver pin PA0
  MainTim2->attachInterrupt(2, T2C2_capt);  //VP speed sensor phase B
  MainTim2->attachInterrupt(3, T2C3_capt);  //Crank Pos sensor capture PA9
  MainTim2->attachInterrupt(4, T2C4_capt);  //solenoid current 'BLIP' detector

  //*******start timer 2 **********
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  TIM8->CCMR1 = 0x0000;  //T2C1 force comp out low. T2C2 input capture. WAS 40
  TIM8->CCMR2 = 0X3100;  // ch 4 capture N8
  //the two previous steps have to be done before enabling the channels in the next register below
  TIM8->CCER = 0XB000;  // ch1 output compare to pin PA0, ch2 either edge, ch4 capture any edge, ch3 capture any edge was13B1
  TIM8->BDTR = 0x8000;  //Timer 8 is more advanced, requires MOE master output enable set.

  //****** timer8 interrupts enable *********
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
  //***** TIMER 3 SETUP FOR PWM ON CH 1, 3 *********
  //*******controls fuel solenoid current, buck converter
  GPIOC->AFR[0] |= 0x02000000;  //AF2; PC6 mapped to Timer 3 ch 1 compare
  GPIOC->AFR[1] |= 0x00000002;  //AF2; PC8 mapped to Timer 3 ch 3 compare, not used
  GPIOC->MODER |= 0x00022000;   //port pins selected as alternate functions

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  TIM3->ARR = 600;       // sets up 120 KHZ PWM
  TIM3->CCMR1 = 0x0060;  // PWM out to ch1
  TIM3->CCMR2 = 0x0060;  // PWM out to ch3
  TIM3->CCER = 0X0101;   // ACTIVE high OUTPUTs ON T3 ch1/ch3 PIN CN10 PC6/PC8 on Nucleo
  TIM3->CCR1 = 200;      //Duty Cycle phase A; just a starting value. Changed later
  TIM3->CCR3 = 200;      //Duty Cycle phase B; just a starting value. Changed later
  TIM3->CR1 |= 0X0001;   //start TIMER3

  //*********** Timer16 setup. PWM channel 1 drives timing piston control valve *****
  //*********** 50 or 60 HZ output mapped to PB6 ************
  //Chanel TIM16_CH1N chosen so PB8 is resevered for CAN_RX future use.
  GPIOB->AFR[0] |= 0x01000000;  //PB6 TIM16 ch1N
  GPIOB->MODER |= 0x00002000;   //PB6 PWM out
  TIM16->CR1 = 0x0004;          // INTERNAL CLK, UEV INT ENABLE, UPCOUNT.
  TIM16->PSC = 1440;            // prescaler 72MHZ / 1440
  TIM16->ARR = 1000;            // sets up 50 60 HZ PWM 100% duty cycle= 1000
  TIM16->CCMR1 = 0x0060;        // PWM out to ch1 PB6
  TIM16->CCER = 0x0004;         // ACTIVE high OUTPUTs
  TIM16->CCR1 = 500;            // DUTY CYCLE, Just a starting value. Changed later
  TIM16->BDTR = 0x8000;         //Timer 16 is more advanced, requires MOE master output enable set.
  TIM16->CR1 |= 0x0001;         // start TIMER16

  //************ Cam position sensor to PA8 setup *******
  attachInterrupt(digitalPinToInterrupt(CMP), Camshaft_handler, CHANGE);

  //********** set up analog systems *******
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    phaseB[phaseB_edge] = TIM2->CCR2;  //record the time of this edge, <think> Lap button on stopwatch

    //************ index tooth detector ********
    // when    PA1 is high  AND    PC9 is low: this is an index tooth
    if (GPIOA->IDR & 0x0002 && !(GPIOC->IDR & 0x0200))  // when phase B(PA1) goes high and phase A(PC9) is low at the same time then trigger
    {                                                   //init a new cycle, <think> reset the stopwatch
      //PB15 sync to O-scope goes high
      scopeHigh;
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
    if (CKP_cnt1 == 30 || CKP_cnt1 == 66) {  //provides a RPM*2 signal to pcm
      //if (CKP_cnt1 == 19 || CKP_cnt1 == 43 || CKP_cnt1 == 67 ){  //was 30 and 66 use for o scope timing analasys
      //Tach signal output PB7 high inverted at connector
      TACHhigh;
    }
    if (CKP_cnt1 == 12 || CKP_cnt1 == 48) {
      //if (CKP_cnt1 == 12 || CKP_cnt1 == 36 ||CKP_cnt1 == 60) {  //was 12 and 48 use for o scope timing analasys
      // PB7 Tach signal low - inverted at conn
      TACHlow;
    }
    CKPpWidth = micros() - lastCKPTime;
    lastCKPTime = micros();

    //*********** CKP missing tooth detector ***********
    if (CKPpWidth > lastCKPpWidth * 3 && !(GPIOA->IDR & 0x0200))  //if PA9 went low and notch was 3X as wide as the previous notch
    {
      CKP_armed = CKP_cnt1;  //armed on this edge. The very next tooth width should be narrower than the last notch
    }
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
void ADC1_setup(void) {
  RCC->CFGR2 |= 0x00000170;  //ADC1,2 clock source 72 MHZ/ 16 .
  //GPIOC->MODER |= 0x00000FFF;    //PC0,1,2,3,4,5 set as analog inputs
  ADC1_2_COMMON->CCR |= 0x00800000;  //enable the internal temp sensor on ADC1 ch 16
  ADC1->CR = 0x00000000;             //turn on Analog voltage regulator sequence
  ADC1->CR |= 0x10000000;
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  ADC1->SMPR1 = 0b00110111110110111110110110110000;  //
  ADC1->SMPR2 = 0b00000110110110110110110110110110;  //181.5 ADC clock cycle sample time

  //                  1 cont. conversions           internal temperature s           amps PC5 ch11           Phase A in PC2          Phase B in PC4
  ADC1->SQR1 |= (0b0000 << ADC_SQR1_L_Pos) | (16 << ADC_SQR1_SQ1_Pos);  // | (11 << ADC_SQR1_SQ2_Pos) | (8 << ADC_SQR1_SQ3_Pos) | (5 << ADC_SQR1_SQ4_Pos);
  //                      TPS PC0 ch6                MAP PC1 ch7
  //ADC1 -> SQR2 |= (6 << ADC_SQR2_SQ5_Pos) | (7 << ADC_SQR2_SQ6_Pos);

  ADC1->CR |= ADC_CR_ADSTART;  //start scanning
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
void ADC2_setup(void) {
  RCC->CFGR2 |= 0x00000170;    //ADC1,2 clock source 72 MHZ/ 16 .
  GPIOC->MODER |= 0x00000FFF;  //PC0,1,2,3,4,5 set as analog inputs
  ADC2->CR = 0x00000000;       //turn on Analog voltage regulator sequence
  ADC2->CR |= 0x10000000;
  delay(1);
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  ADC2->SMPR1 = 0b00110111110110111110110110110000;  //
  ADC2->SMPR2 = 0b00000110110110110110110110110110;  //181.5 ADC clock cycle sample time

  //                  6 cont. conversions           volts PC3 ch 9            amps PC5 ch11           Phase A in PC2          Phase B in PC4
  ADC2->SQR1 |= (0b0101 << ADC_SQR1_L_Pos) | (9 << ADC_SQR1_SQ1_Pos) | (11 << ADC_SQR1_SQ2_Pos) | (8 << ADC_SQR1_SQ3_Pos) | (5 << ADC_SQR1_SQ4_Pos);
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
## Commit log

2024-10-31 Update README.md
    inital
2024-11-01 name
    PCB gerbers
2024-11-01 PCB gerbers
2024-11-04 renamed
2024-11-04 Update LICENSE
2024-11-05 Updated
    include link
2024-11-24 updated
    Part numbers. fixed missing R13 & R14
2024-12-05 new version 1.1
2025-10-21 KiCad project
